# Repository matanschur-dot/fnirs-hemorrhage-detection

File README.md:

# Hardware-compatible synthetic fNIRS dataset generator

This project generates matched healthy/hemorrhage synthetic samples for the supplied PCB:

- **16 LEDs total**: 8 at 740 nm and 8 at 850 nm
- **16 photodetectors**
- `I740.shape == (8, 16)`
- `I850.shape == (8, 16)`

The package stops at dataset generation. It does **not** contain MedT or any learning model.

## What is implemented

1. KiCad PCB parsing and exact hardware validation.
2. Fixed channel order and 256 source-detector channel map.
3. Flat layered phantom with a real air layer: air, scalp, skull, CSF, brain.
4. Matched healthy/hemorrhage anatomy from one subject.
5. Controlled hemorrhage depth (default 5–20 mm from the air/scalp boundary), size, and x-y sensor coverage.
6. Separate 740/850 optical-property tables with paired subject-level variation.
7. PMCX runner: 8 sources × 16 detectors per wavelength.
8. `sphere_mean` detector extraction, isolated behind a replaceable detector interface.
9. Optional noise (`none` or `basic`).
10. Atomic sample saving, resume, CSV metadata, logs, ETA, and pilot visualizations.

## Important scientific limitation

The current model is a **flat layered phantom**, not an anatomical human head. The detector measurement uses local PMCX flux averaged around the detector as an engineering approximation. These assumptions must be reported in the project and later validated against the physical phantom/hardware.

The included `analytic_debug` backend is only a software smoke test. It is **not Monte Carlo data and must never be used to train the model**.

## Installation

```bash
python -m venv .venv
# Windows:
.venv\Scripts\activate
# Linux/macOS:
source .venv/bin/activate

pip install -r requirements.txt
pip install pmcx
```

PMCX requires a compatible NVIDIA CUDA environment. Verify it on the target computer:

```bash
python -c "import pmcx; print('PMCX imported successfully')"
```

## Validate PCB and tests

The supplied PCB is included as `fnirs.kicad_pcb`.

```bash
python run_geometry_validation.py --pcb fnirs.kicad_pcb --output output/geometry
```

Run all tests against the actual PCB:

**Windows PowerShell**

```powershell
$env:FNIRS_TEST_PCB="fnirs.kicad_pcb"
python -m pytest tests -v
```

**Linux/macOS**

```bash
FNIRS_TEST_PCB=fnirs.kicad_pcb python -m pytest tests -v
```

## First: software-only smoke test

This checks files, shapes, logs, resume, and plots. It is not physical data:

```bash
python run_optical_pilot.py --pcb fnirs.kicad_pcb --output output/debug_smoke --num-subjects 1 --backend analytic_debug --photons 1000 --noise-mode none
```

## Then: real PMCX pilot

Start with one pair and a low photon count:

```bash
python run_optical_pilot.py --pcb fnirs.kicad_pcb --output output/pmcx_pilot_1 --num-subjects 1 --backend pmcx --photons 100000 --noise-mode none
```

When this succeeds, inspect:

- `samples/*.npz`
- `metadata.csv`
- `generation.log`
- `visualizations/*_optical_pair.png`

Then generate 5–20 pilot pairs:

```bash
python run_optical_pilot.py --pcb fnirs.kicad_pcb --output output/pmcx_pilot_10 --num-subjects 10 --backend pmcx --photons 500000 --noise-mode none --resume
```

## Production generation

Only after the pilot has been reviewed:

```bash
python generate_optical_dataset.py --pcb fnirs.kicad_pcb --output data/fnirs_synthetic --num-subjects 1000 --backend pmcx --photons 2000000 --noise-mode basic --resume
```

Each subject creates two samples, one healthy and one hemorrhage. Thus `--num-subjects 1000` creates 2,000 files and performs 32 PMCX source simulations per subject.

## Runtime progress

The generator prints and writes to `generation.log`:

- subject index;
- healthy/hemorrhage case;
- wavelength;
- source index;
- completed PMCX runs;
- source runtime;
- estimated remaining time;
- pair runtime and optical difference.

A completed pair is saved before the next pair begins. `--resume` skips valid completed pairs.

## Sample contents

Every `.npz` includes:

- `I740`, `I850`;
- label, subject/pair/sample IDs;
- tissue volume, brain mask, 3D hemorrhage mask;
- hemorrhage center, radii, depth, and volume;
- all source and detector positions;
- 740/850 optical properties;
- seeds, photon count, versions, backend, and noise mode.

Load without pickle:

```python
import numpy as np
with np.load("sample.npz", allow_pickle=False) as d:
    print(d["I740"].shape, d["I850"].shape)
```

## Verified vs. not verified in this delivery

Verified in the provided environment:

- package imports;
- actual PCB parsing and 16/16 hardware validation;
- all unit tests;
- anatomy pairing and air layer;
- full end-to-end file generation using `analytic_debug`;
- output shapes, metadata, plots, logs, and atomic writes.

Not executable in the provided environment because PMCX/CUDA was unavailable:

- a real PMCX run and the exact runtime on the user's GPU;
- the installed PMCX version's exact returned field and numerical scale.

The PMCX integration follows the API used in the user's earlier scripts (`pmcx.run`, `flux`/`data`, summing the time dimension). Run the one-pair PMCX pilot before any large generation. If the installed PMCX version returns a different field or shape, the runner raises a clear error instead of silently writing invalid samples.

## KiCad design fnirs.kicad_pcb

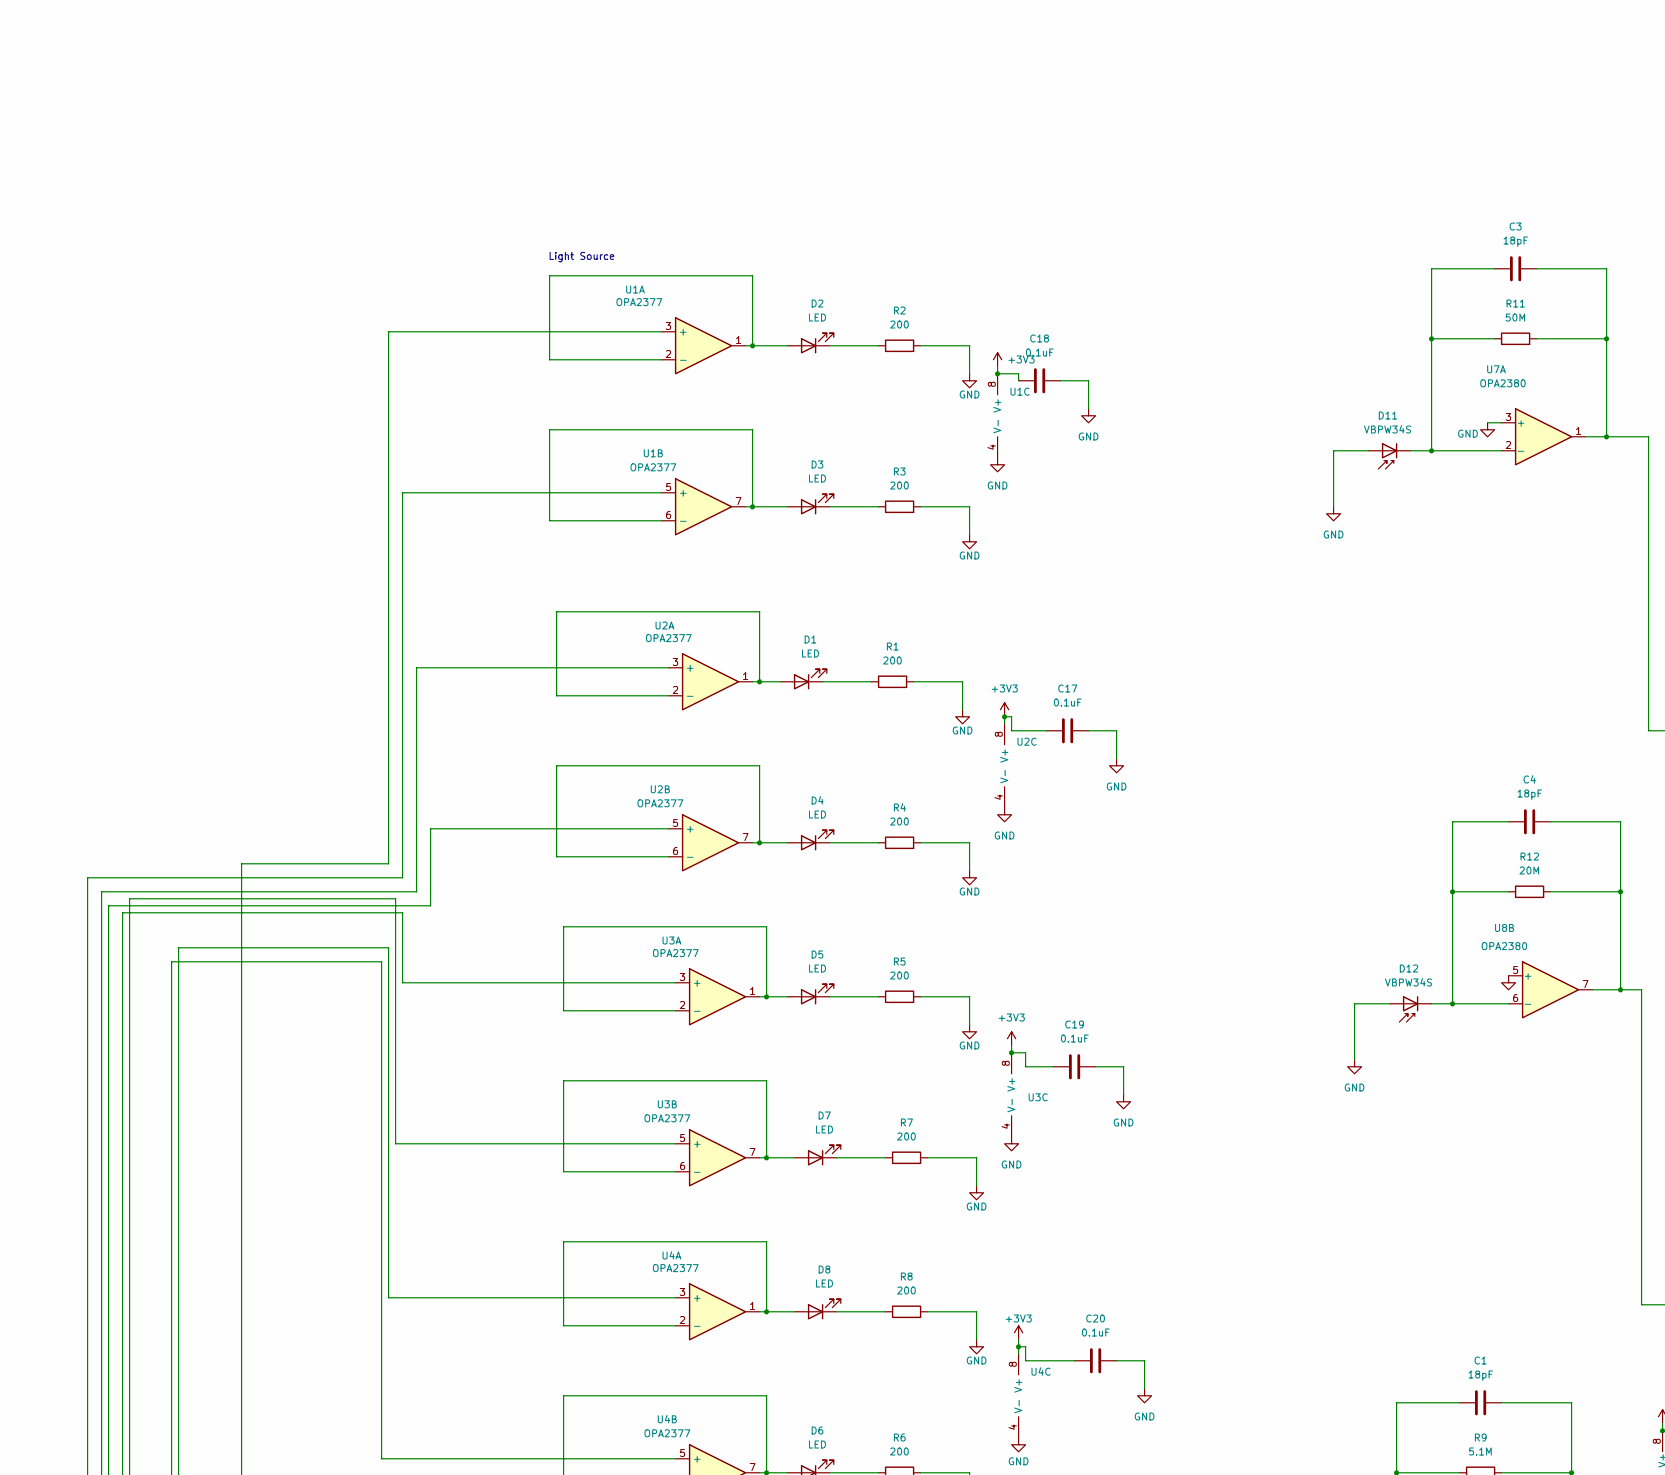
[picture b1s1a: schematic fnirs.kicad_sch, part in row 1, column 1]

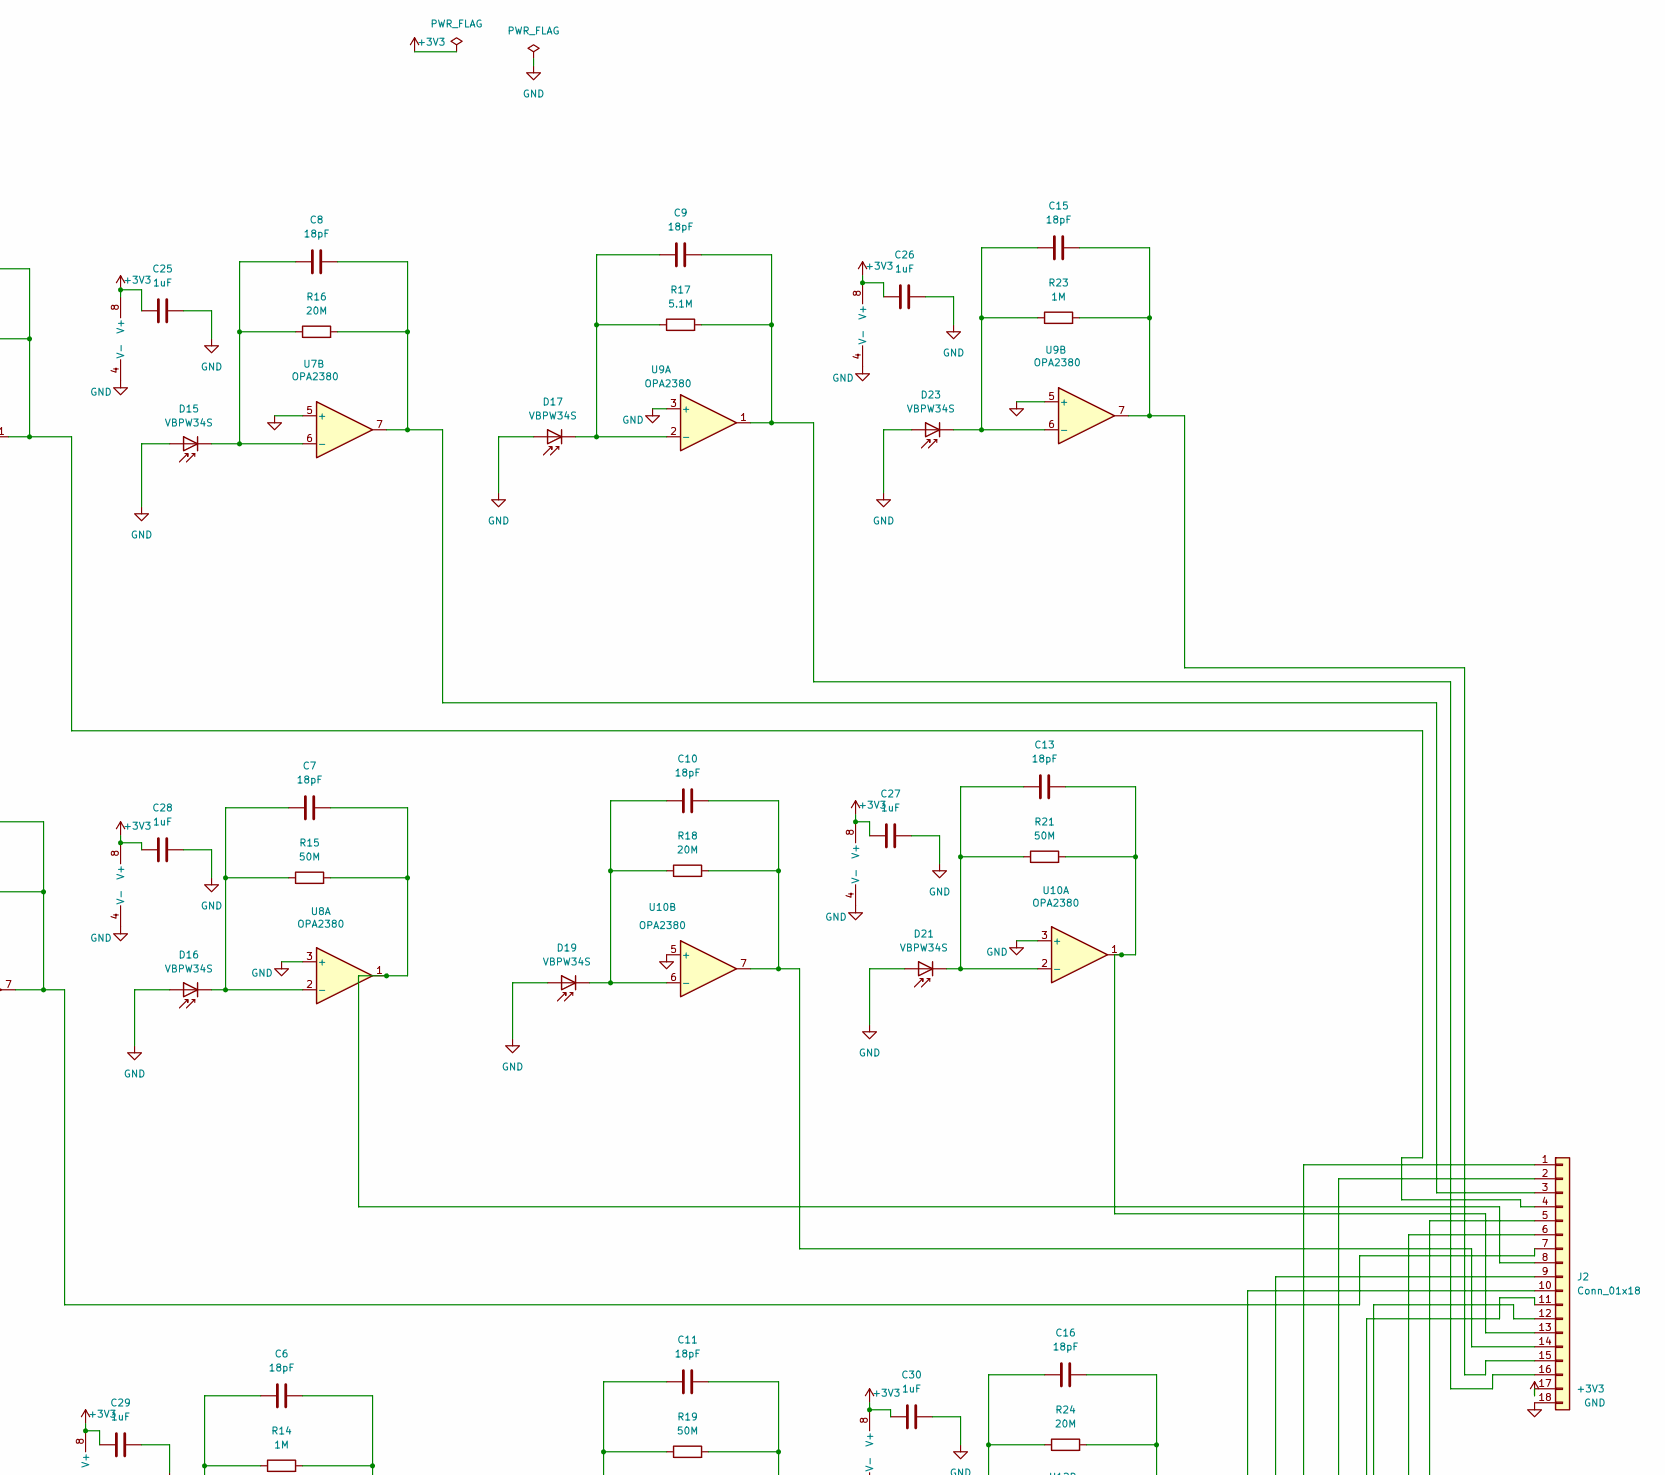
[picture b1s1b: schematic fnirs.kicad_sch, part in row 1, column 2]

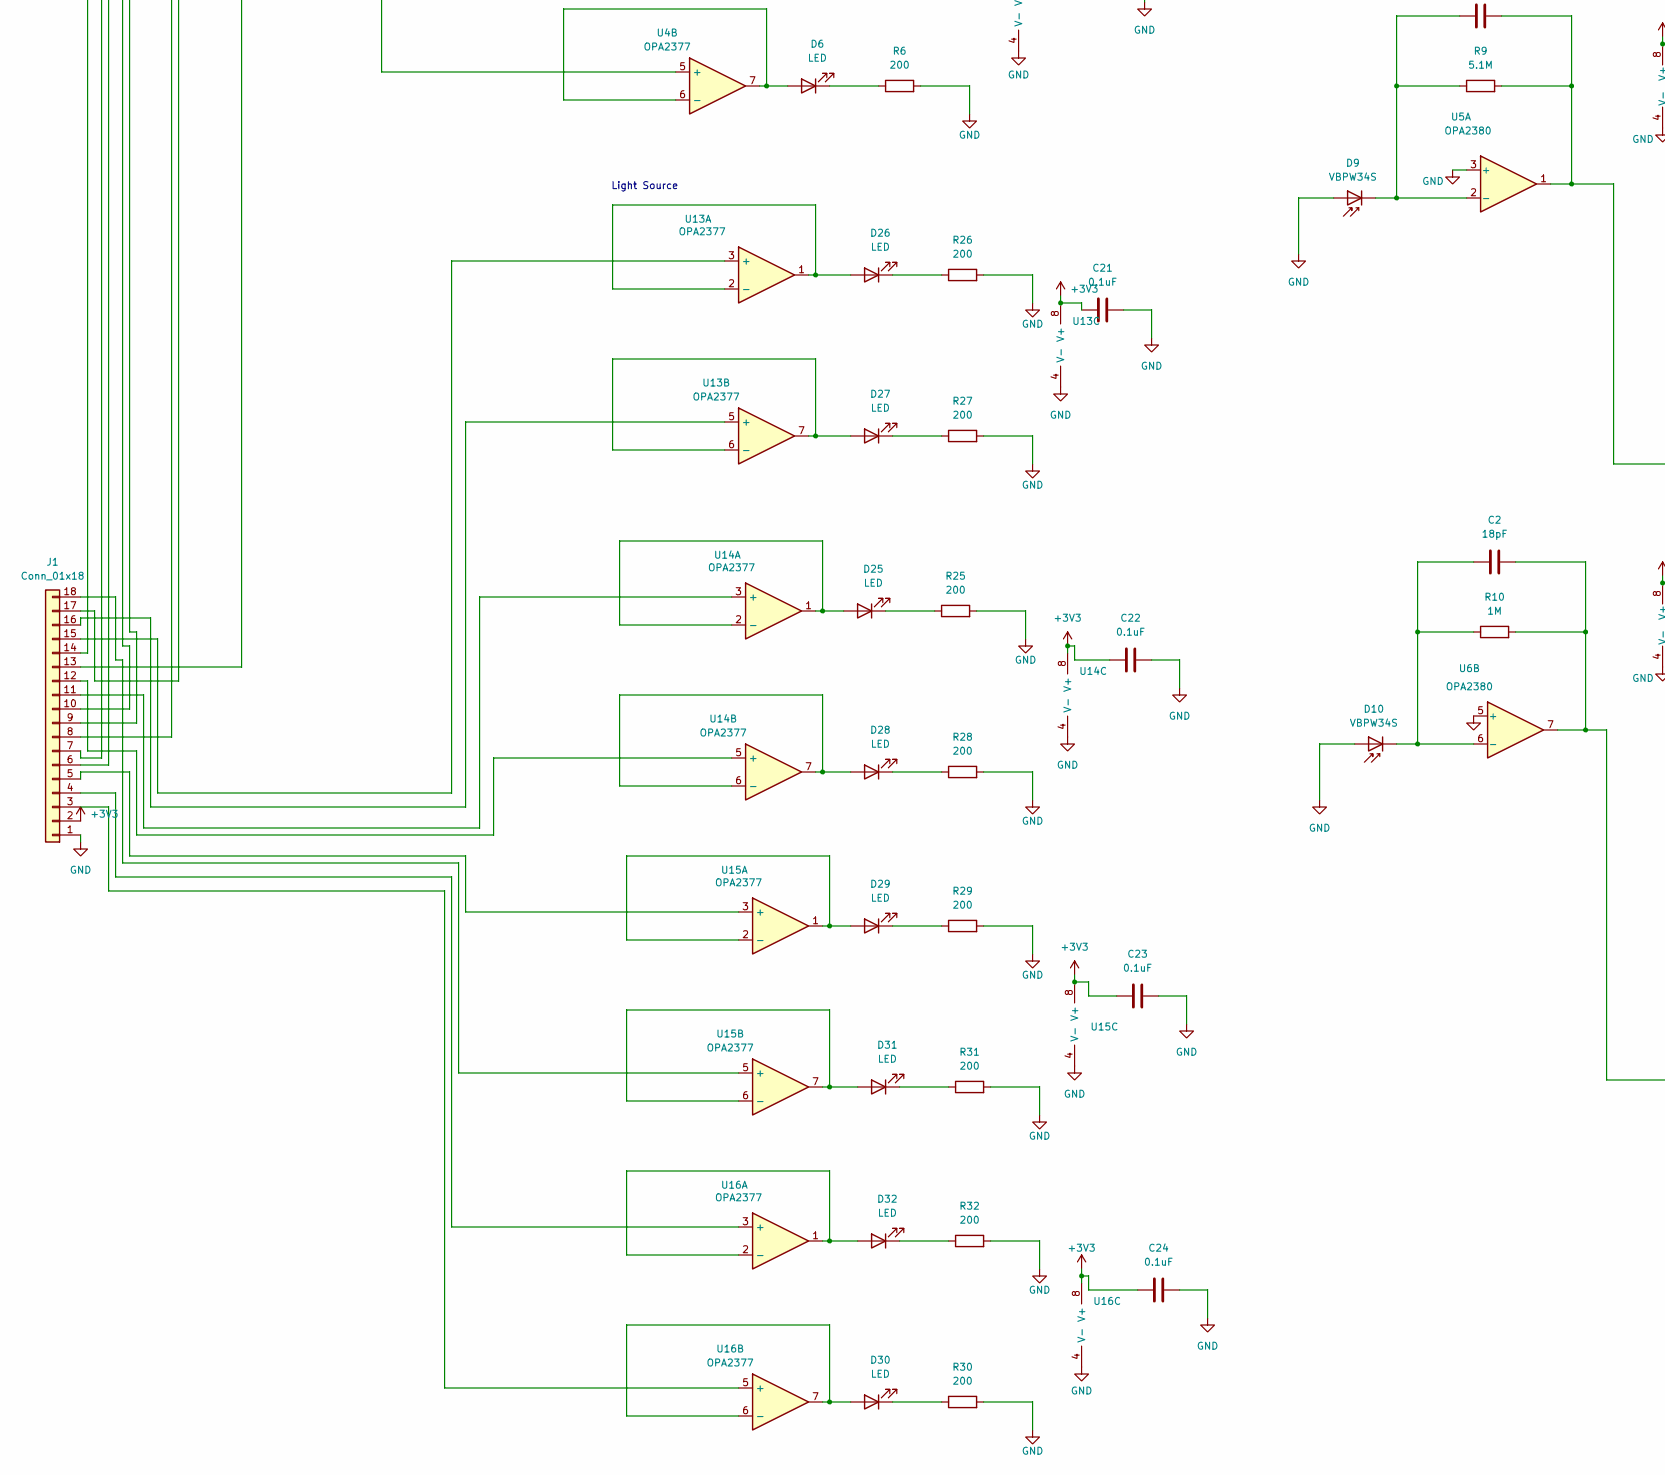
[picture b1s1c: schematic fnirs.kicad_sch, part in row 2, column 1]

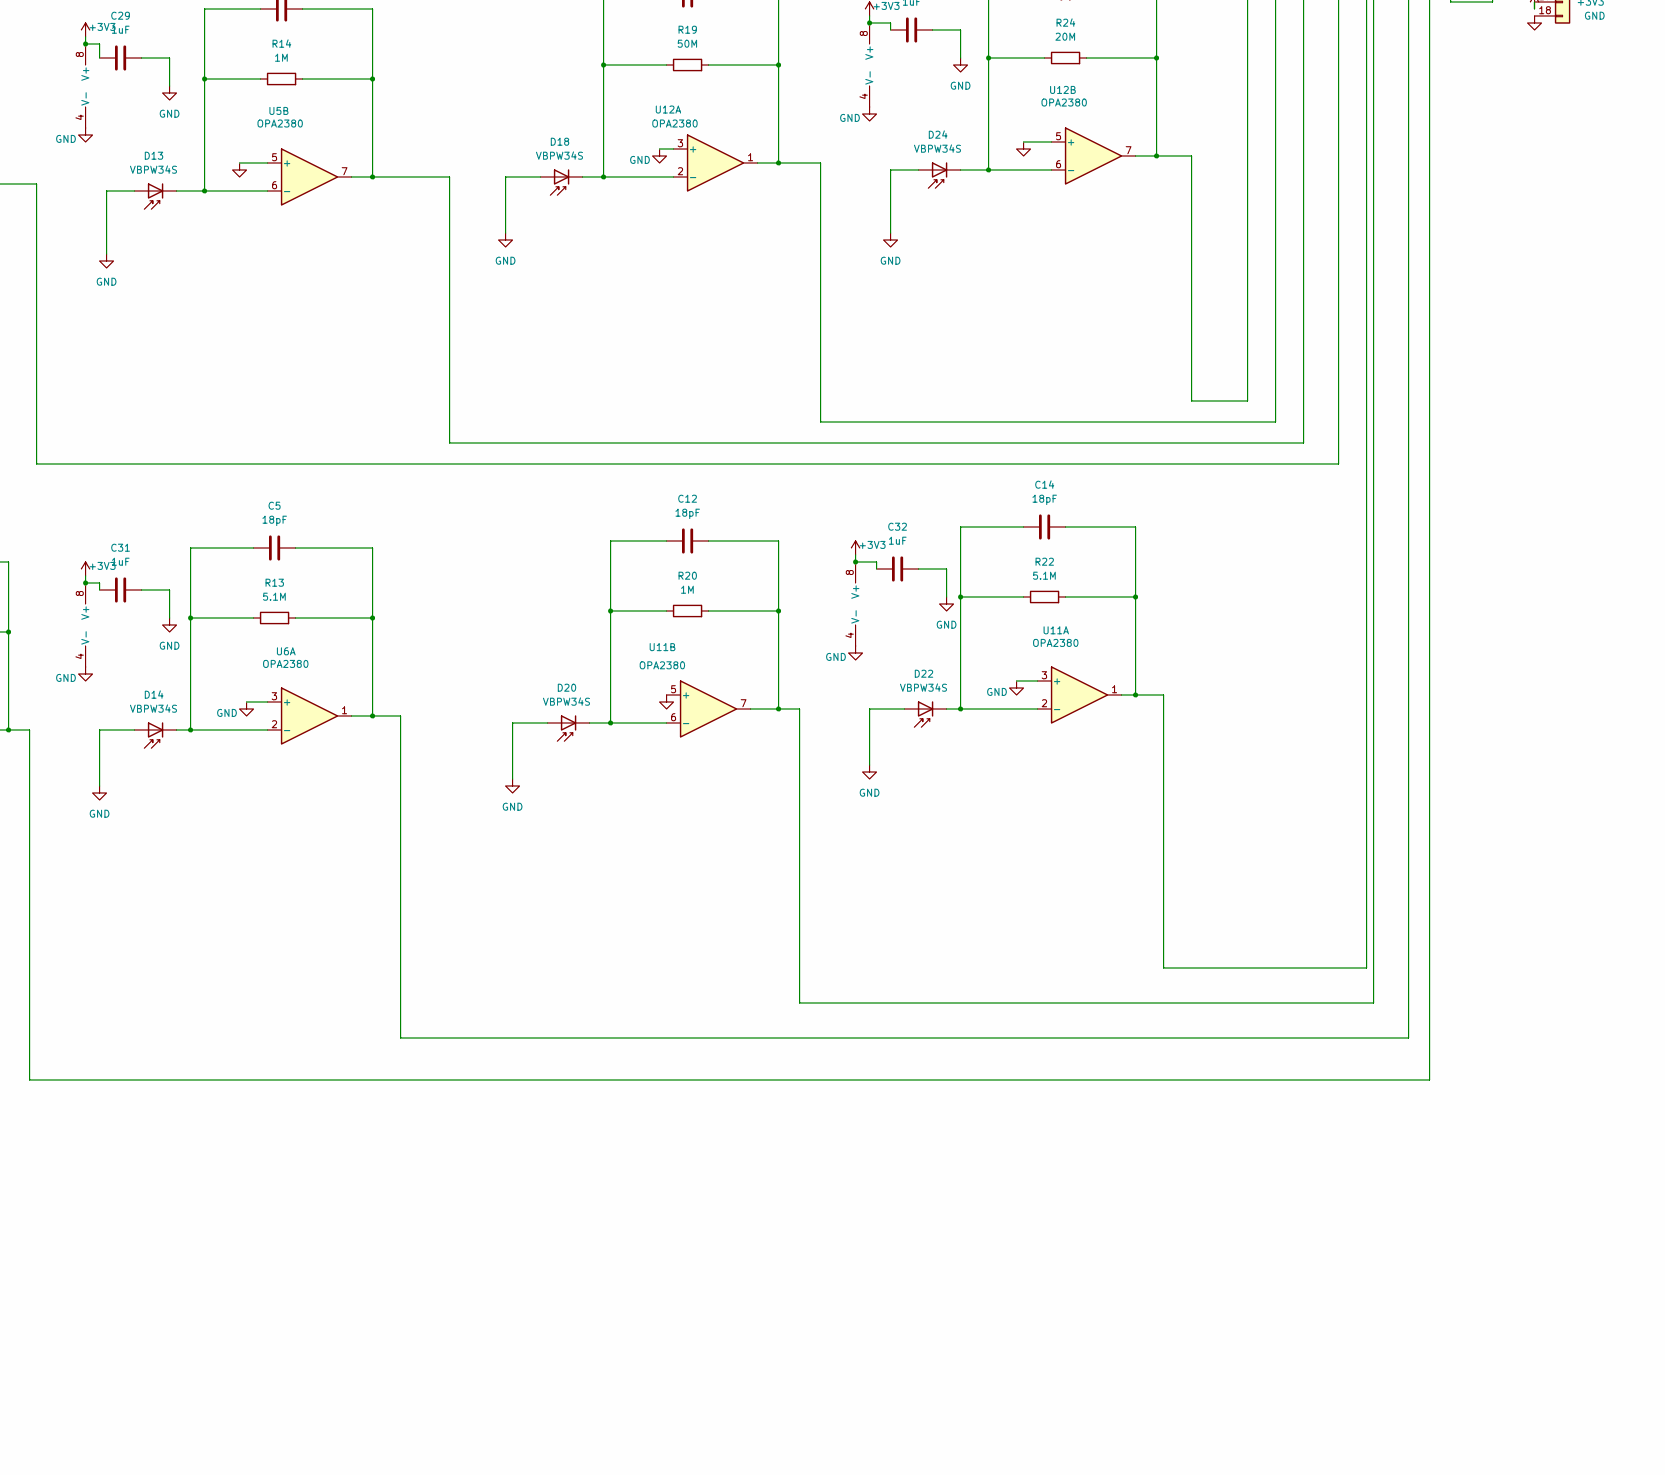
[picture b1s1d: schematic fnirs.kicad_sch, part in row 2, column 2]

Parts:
C1, C2, C3, C4, C5, C6, C7, C8, C9, C10, C11, C12, C13, C14, C15, C16: 18pF; C_0603_1608Metric
C17, C18, C19, C20, C21, C22, C23, C24: 0.1uF; C_0603_1608Metric_Pad1.08x0.95mm_HandSolder
C25, C26, C27, C28, C29, C30, C31, C32: 1uF; C_0603_1608Metric_Pad1.08x0.95mm_HandSolder
D1, D2, D3, D4, D5, D6, D7, D8, D25, D26, D27, D28, D29, D30, D31, D32: LED; LED_1206_3216Metric
D9, D10, D11, D12, D13, D14, D15, D16, D17, D18, D19, D20, D21, D22, D23, D24: VBPW34S; Osram_BPW34S-SMD
J1, J2: Conn_01x18; PinHeader_1x18_P2.54mm_Vertical
R1, R2, R3, R4, R5, R6, R7, R8, R25, R26, R27, R28, R29, R30, R31, R32: 200; R_0603_1608Metric
R9, R13, R17, R22: 5.1M; R_0603_1608Metric
R10, R14, R20, R23: 1M; R_0603_1608Metric
R11, R15, R19, R21: 50M; R_0603_1608Metric
R12, R16, R18, R24: 20M; R_0603_1608Metric
U1, U2, U3, U4, U13, U14, U15, U16: OPA2377; SOIC-8_3.9x4.9mm_P1.27mm
U5, U6, U7, U8, U9, U10, U11, U12: OPA2380; SOIC-8_3.9x4.9mm_P1.27mm

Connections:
+3V3: C17.1, C18.1, C19.1, C20.1, C21.1, C22.1, C23.1, C24.1, C25.1, C26.1, C27.1, C28.1, C29.1, C30.1, C31.1, C32.1, J1.2, J2.17, U1.8 (V+), U2.8 (V+), U3.8 (V+), U4.8 (V+), U5.8 (V+), U6.8 (V+), U7.8 (V+), U8.8 (V+), U9.8 (V+), U10.8 (V+), U11.8 (V+), U12.8 (V+), U13.8 (V+), U14.8 (V+), U15.8 (V+), U16.8 (V+)
GND: C17.2, C18.2, C19.2, C20.2, C21.2, C22.2, C23.2, C24.2, C25.2, C26.2, C27.2, C28.2, C29.2, C30.2, C31.2, C32.2, D9.2 (A), D10.2 (A), D11.2 (A), D12.2 (A), D13.2 (A), D14.2 (A), D15.2 (A), D16.2 (A), D17.2 (A), D18.2 (A), D19.2 (A), D20.2 (A), D21.2 (A), D22.2 (A), D23.2 (A), D24.2 (A), J1.1, J2.18, R1.2, R2.2, R3.2, R4.2, R5.2, R6.2, R7.2, R8.2, R25.2, R26.2, R27.2, R28.2, R29.2, R30.2, R31.2, R32.2, U1.4 (V-), U2.4 (V-), U3.4 (V-), U4.4 (V-), U5.3 (+), U5.4 (V-), U5.5 (+), U6.3 (+), U6.4 (V-), U6.5 (+), U7.3 (+), U7.4 (V-), U7.5 (+), U8.3 (+), U8.4 (V-), U8.5 (+), U9.3 (+), U9.4 (V-), U9.5 (+), U10.3 (+), U10.4 (V-), U10.5 (+), U11.3 (+), U11.4 (V-), U11.5 (+), U12.3 (+), U12.4 (V-), U12.5 (+), U13.4 (V-), U14.4 (V-), U15.4 (V-), U16.4 (V-)
unnamed: D1.2 (A), U2.1, U2.2 (-)
unnamed: D1.1 (K), R1.1
unnamed: D2.2 (A), U1.1, U1.2 (-)
unnamed: D2.1 (K), R2.1
unnamed: D3.2 (A), U1.6 (-), U1.7
unnamed: D3.1 (K), R3.1
unnamed: D4.2 (A), U2.6 (-), U2.7
unnamed: D4.1 (K), R4.1
unnamed: D5.2 (A), U3.1, U3.2 (-)
unnamed: D5.1 (K), R5.1
unnamed: D6.2 (A), U4.6 (-), U4.7
unnamed: D6.1 (K), R6.1
unnamed: D7.2 (A), U3.6 (-), U3.7
unnamed: D7.1 (K), R7.1
unnamed: D8.2 (A), U4.1, U4.2 (-)
unnamed: D8.1 (K), R8.1
unnamed: C1.1, D9.1 (K), R9.1, U5.2 (-)
unnamed: C2.1, D10.1 (K), R10.1, U6.6 (-)
unnamed: C3.1, D11.1 (K), R11.1, U7.2 (-)
unnamed: C4.1, D12.1 (K), R12.1, U8.6 (-)
unnamed: C6.1, D13.1 (K), R14.1, U5.6 (-)
unnamed: C5.1, D14.1 (K), R13.1, U6.2 (-)
unnamed: C8.1, D15.1 (K), R16.1, U7.6 (-)
unnamed: C7.1, D16.1 (K), R15.1, U8.2 (-)
unnamed: C9.1, D17.1 (K), R17.1, U9.2 (-)
unnamed: C11.1, D18.1 (K), R19.1, U12.2 (-)
unnamed: C10.1, D19.1 (K), R18.1, U10.6 (-)
unnamed: C12.1, D20.1 (K), R20.1, U11.6 (-)
unnamed: C13.1, D21.1 (K), R21.1, U10.2 (-)
unnamed: C14.1, D22.1 (K), R22.1, U11.2 (-)
unnamed: C15.1, D23.1 (K), R23.1, U9.6 (-)
unnamed: C16.1, D24.1 (K), R24.1, U12.6 (-)
unnamed: D25.2 (A), U14.1, U14.2 (-)
unnamed: D25.1 (K), R25.1
unnamed: D26.2 (A), U13.1, U13.2 (-)
unnamed: D26.1 (K), R26.1
unnamed: D27.2 (A), U13.6 (-), U13.7
unnamed: D27.1 (K), R27.1
unnamed: D28.2 (A), U14.6 (-), U14.7
unnamed: D28.1 (K), R28.1
unnamed: D29.2 (A), U15.1, U15.2 (-)
unnamed: D29.1 (K), R29.1
unnamed: D30.2 (A), U16.6 (-), U16.7
unnamed: D30.1 (K), R30.1
unnamed: D31.2 (A), U15.6 (-), U15.7
unnamed: D31.1 (K), R31.1
unnamed: D32.2 (A), U16.1, U16.2 (-)
unnamed: D32.1 (K), R32.1
unnamed: J1.3, U16.5 (+)
unnamed: J1.4, U16.3 (+)
unnamed: J1.5, U15.3 (+)
unnamed: J1.6, U2.5 (+)
unnamed: J1.7, U2.3 (+)
unnamed: J1.8, U4.5 (+)
unnamed: J1.9, U3.5 (+)
unnamed: J1.10, U3.3 (+)
unnamed: J1.11, U14.3 (+)
unnamed: J1.12, U14.5 (+)
unnamed: J1.13, U1.3 (+)
unnamed: J1.14, U1.5 (+)
unnamed: J1.15, U13.3 (+)
unnamed: J1.16, U13.5 (+)
unnamed: J1.17, U4.3 (+)
unnamed: J1.18, U15.5 (+)
unnamed: C6.2, J2.1, R14.2, U5.7
unnamed: C1.2, J2.2, R9.2, U5.1
unnamed: C8.2, J2.3, R16.2, U7.7
unnamed: C3.2, J2.4, R11.2, U7.1
unnamed: C2.2, J2.5, R10.2, U6.7
unnamed: C5.2, J2.6, R13.2, U6.1
unnamed: C4.2, J2.7, R12.2, U8.7
unnamed: C7.2, J2.8, R15.2, U8.1
unnamed: C11.2, J2.9, R19.2, U12.1
unnamed: C16.2, J2.10, R24.2, U12.7
unnamed: C14.2, J2.11, R22.2, U11.1
unnamed: C12.2, J2.12, R20.2, U11.7
unnamed: C13.2, J2.13, R21.2, U10.1
unnamed: C10.2, J2.14, R18.2, U10.7
unnamed: C15.2, J2.15, R23.2, U9.7
unnamed: C9.2, J2.16, R17.2, U9.1

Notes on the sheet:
Light Source

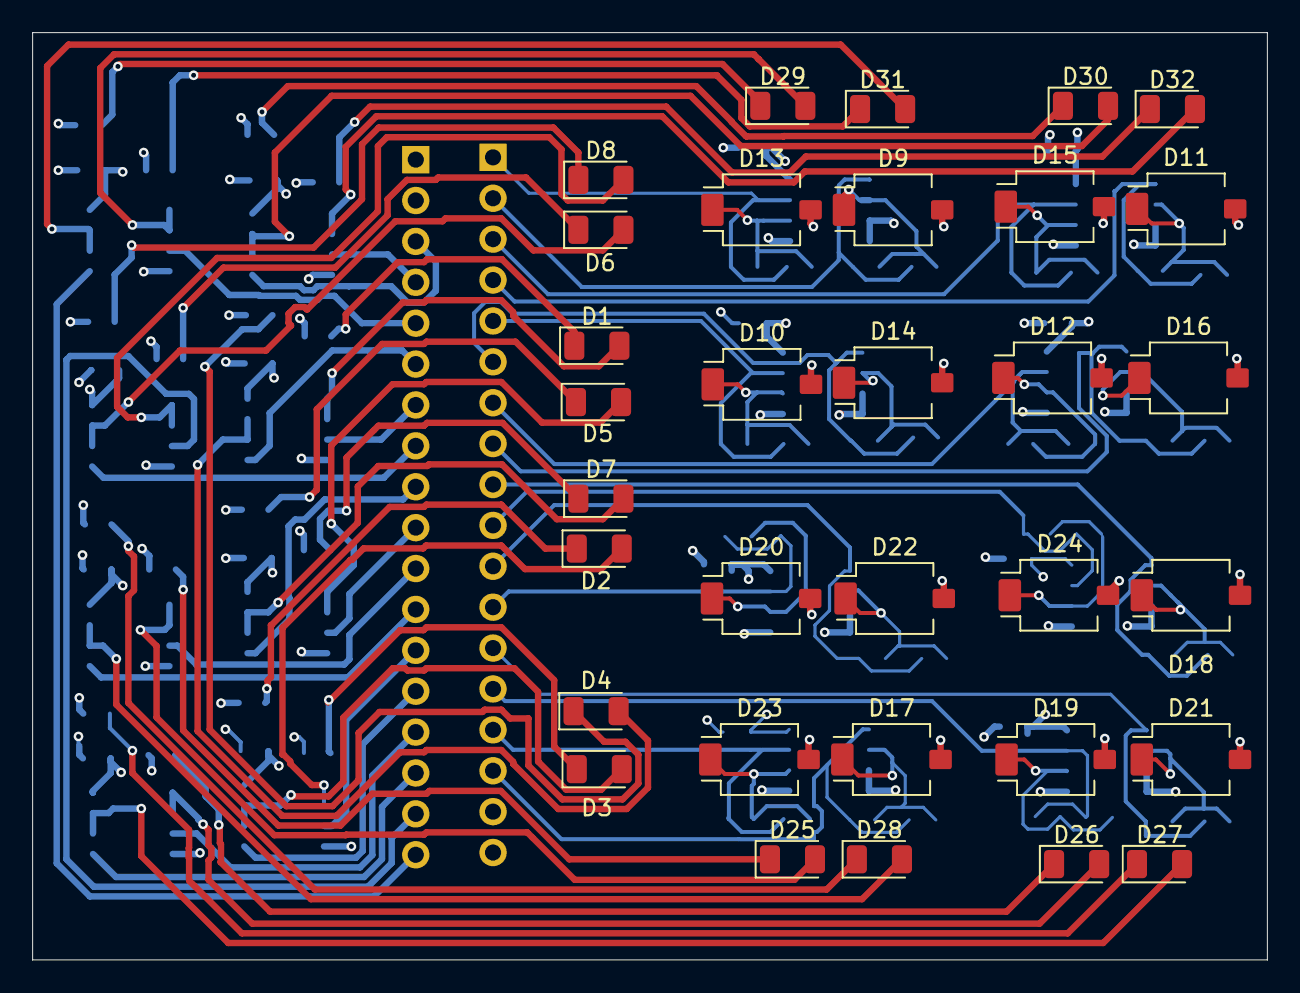
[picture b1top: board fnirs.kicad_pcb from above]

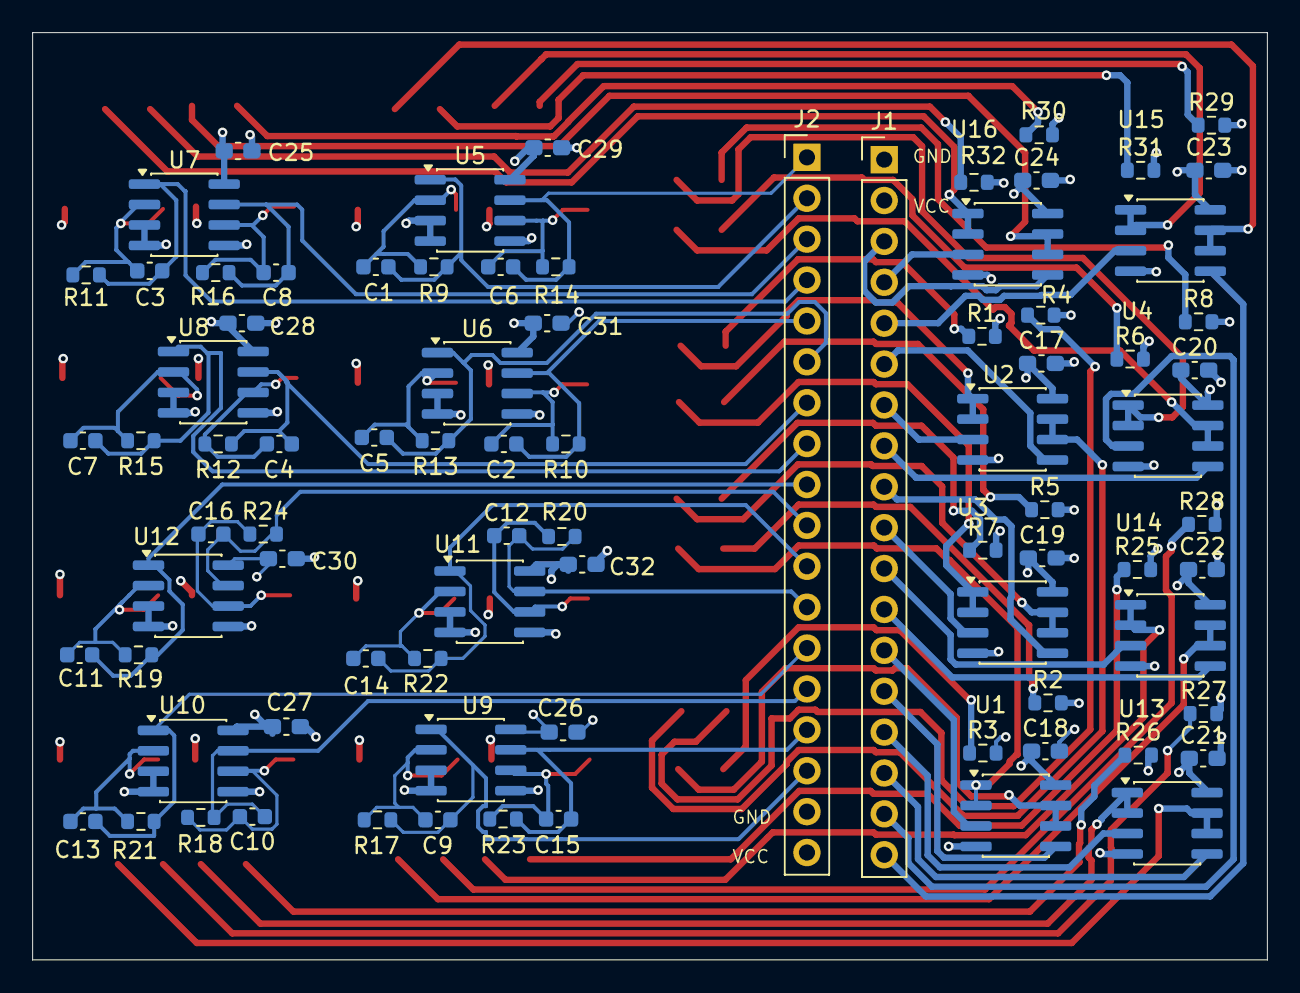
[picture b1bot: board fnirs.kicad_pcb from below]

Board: 4 copper layers, 76.7 x 57.6 mm, 114 parts (82 on the bottom side), 82 nets.
